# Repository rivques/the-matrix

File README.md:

# the-matrix

This is a large (theoretically 1ftx1ft) LED matrix display with a resolution of up to 120x120 monochrome pixels. My intended use for it is to act as an "ultra-clock," showing not just the time but also other useful information like weather, sports scores, maybe news, etc. However, it should be said that this is designed to be a generic module, and not destined for any specific project - this should be something I can pull off my shelf, send the correct control signals to, and get a display from.

I've had the ultra-clock idea for a while, and I originally wanted to use flip dots for the display, but they turned out to be expensive and hard to find, so I switched to using LED matrices instead.

The full display is constructed of 9 display modules, each of which itself contains 25 8x8 LED matrices. Each module also contains positions for the shift registers and MOSFETs that make up the control circuitry.

However, I have not yet built the full display - scaling up from 1 to 9 modules turned out to be _much_ harder than expected. I have 4 modules fully built, plus harnesses and a control board - I just haven't been able to make them play nice, despite spending more than 20 hours on scaling and troubleshooting. I still hope to realize the full vision at some point, but I'm pretty burnt out on this for the short term.

The display is not without its quirks. Most of these stem from either the geometric realities of trying to fit everything onto the board or a software-compensatable routing mistake that would take hours of work to fix in hardware. The biggest of these is that the current-limiting resistors aren't actually on the board but instead fly above the back of it. Also, the bottom and top row of matrices on each module are rotated 90 degrees, and every other module has pairs of rows and columns swapped (e.g. col1 connects to col2, col2->col1, col3->col4, etc.) This is something I can fix in software.

The display will probably be driven by a Pi Pico W or an ESP32, but especially if high framerates are not required it could be also driven by something less powerful. The driver connects to each row and column via the row control and column control pads.

One of the things I hope to learn from this board is where the limits actually lie when I try to drive things at high frequencies. I don't know how scared to be of things like ringing or EMI, and I'll probably find out.

The theoretical max framerate for this board is something like 4096fps, which would probably be implemented as 16fps with 255-tick BCM dimming, though this would require driving the clock line at something like 4MHz, and I have no idea if that'll be possible. If it's not, I can derate to something like 8fps with 7-tick dimming, which would be ~64fps or a much more manageable 60kHz clock frequency.

Here's a render of the back of the a single display module (the front is just a grid of matrices, which I don't have a 3D model for but I'm sure you can imagine). For more pictures, including the schematic and each internal layer, check out the [journal](https://github.com/rivques/the-matrix/blob/main/JOURNAL.md#may-29th).

BOM (for some parts I'm getting spares since they'd be a pain to source if some turn out to be dead on arrival. if this can't be included in the grant i'll happily cover the spares myself):

Part|Quantity|Price/unit|Total price|# pins/unit|# pins total|Note|Link
---|---|---|---|---|---|---|---
788AS 8x8 LED Matrix|230|$0.35|$82.00|16|3600|not going to count on 0% DoA rate here|https://www.aliexpress.us/item/2251832771187101.html
74HC595 Shift Register|15|$0.22|$4.00|16|240|2x20 is cheaper than 3x5|https://www.aliexpress.us/item/3256807421796895.html
TPIC6B595 Shift Register|20|$0.50|$10|16|240|again, not counting on no DoA|https://www.aliexpress.us/item/3256806981485001.html
IRFU9024NPBF MOSFET|125|$0.40|$40.00|3|360||https://www.aliexpress.us/item/3256808251284284.html
220Ω Resistor|120|$0.02|$2.80|2|240|2x100 is cheaper than 12x10|https://www.aliexpress.us/item/2251832766343175.html
2x20 right-angle header female|12|$2.00|$4.00|40|80||https://www.aliexpress.us/item/3256805899201197.html
2x20 right-angle header male|12|$2.50|$5.00|40|80||https://www.aliexpress.us/item/3256804718416281.html
5V 3A Power Supply|1|$4.00|$4.00|2|2||https://www.aliexpress.us/item/3256805577151044.html
Matrix PCB|10|$2.5|$25.00|0|0|i'll buy this separately from the grant so i can combine it with another order|JLCPCB
Total|||$173||4850|total w/o PCB: $148 :tada:

Schematic:

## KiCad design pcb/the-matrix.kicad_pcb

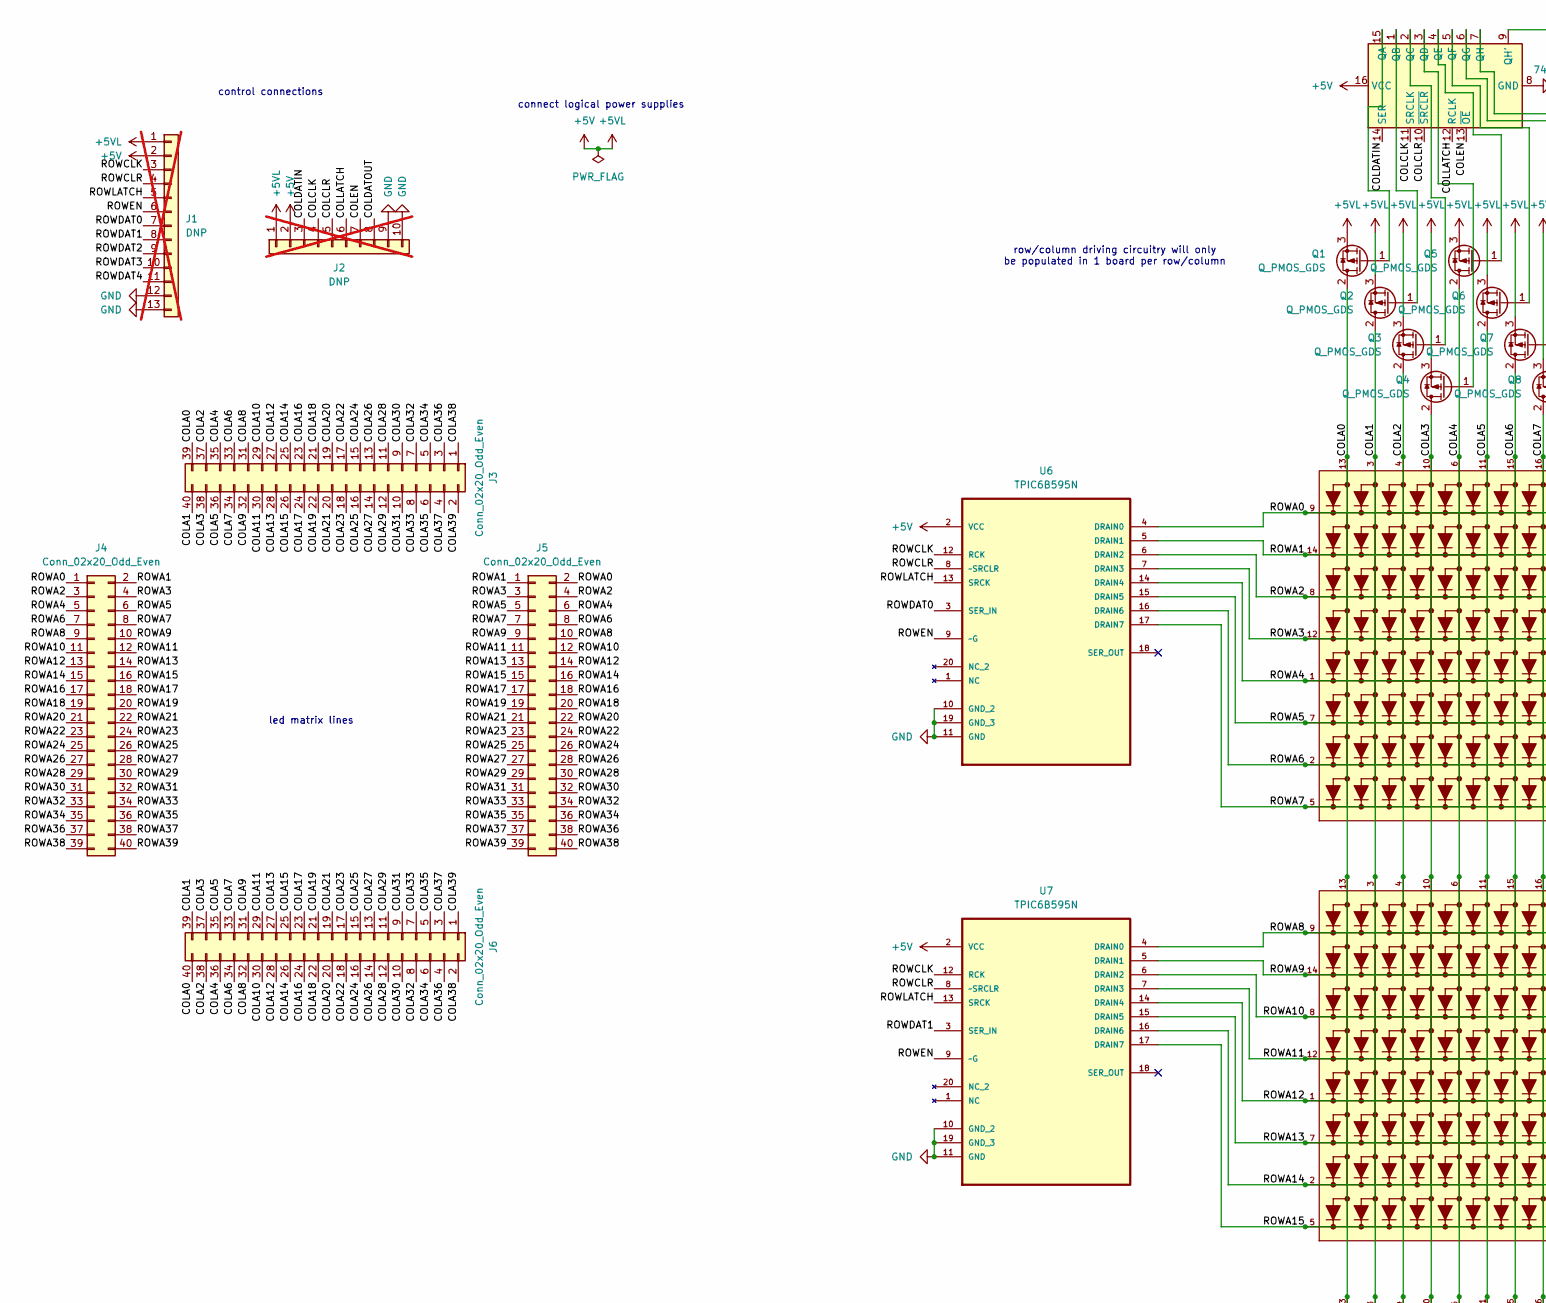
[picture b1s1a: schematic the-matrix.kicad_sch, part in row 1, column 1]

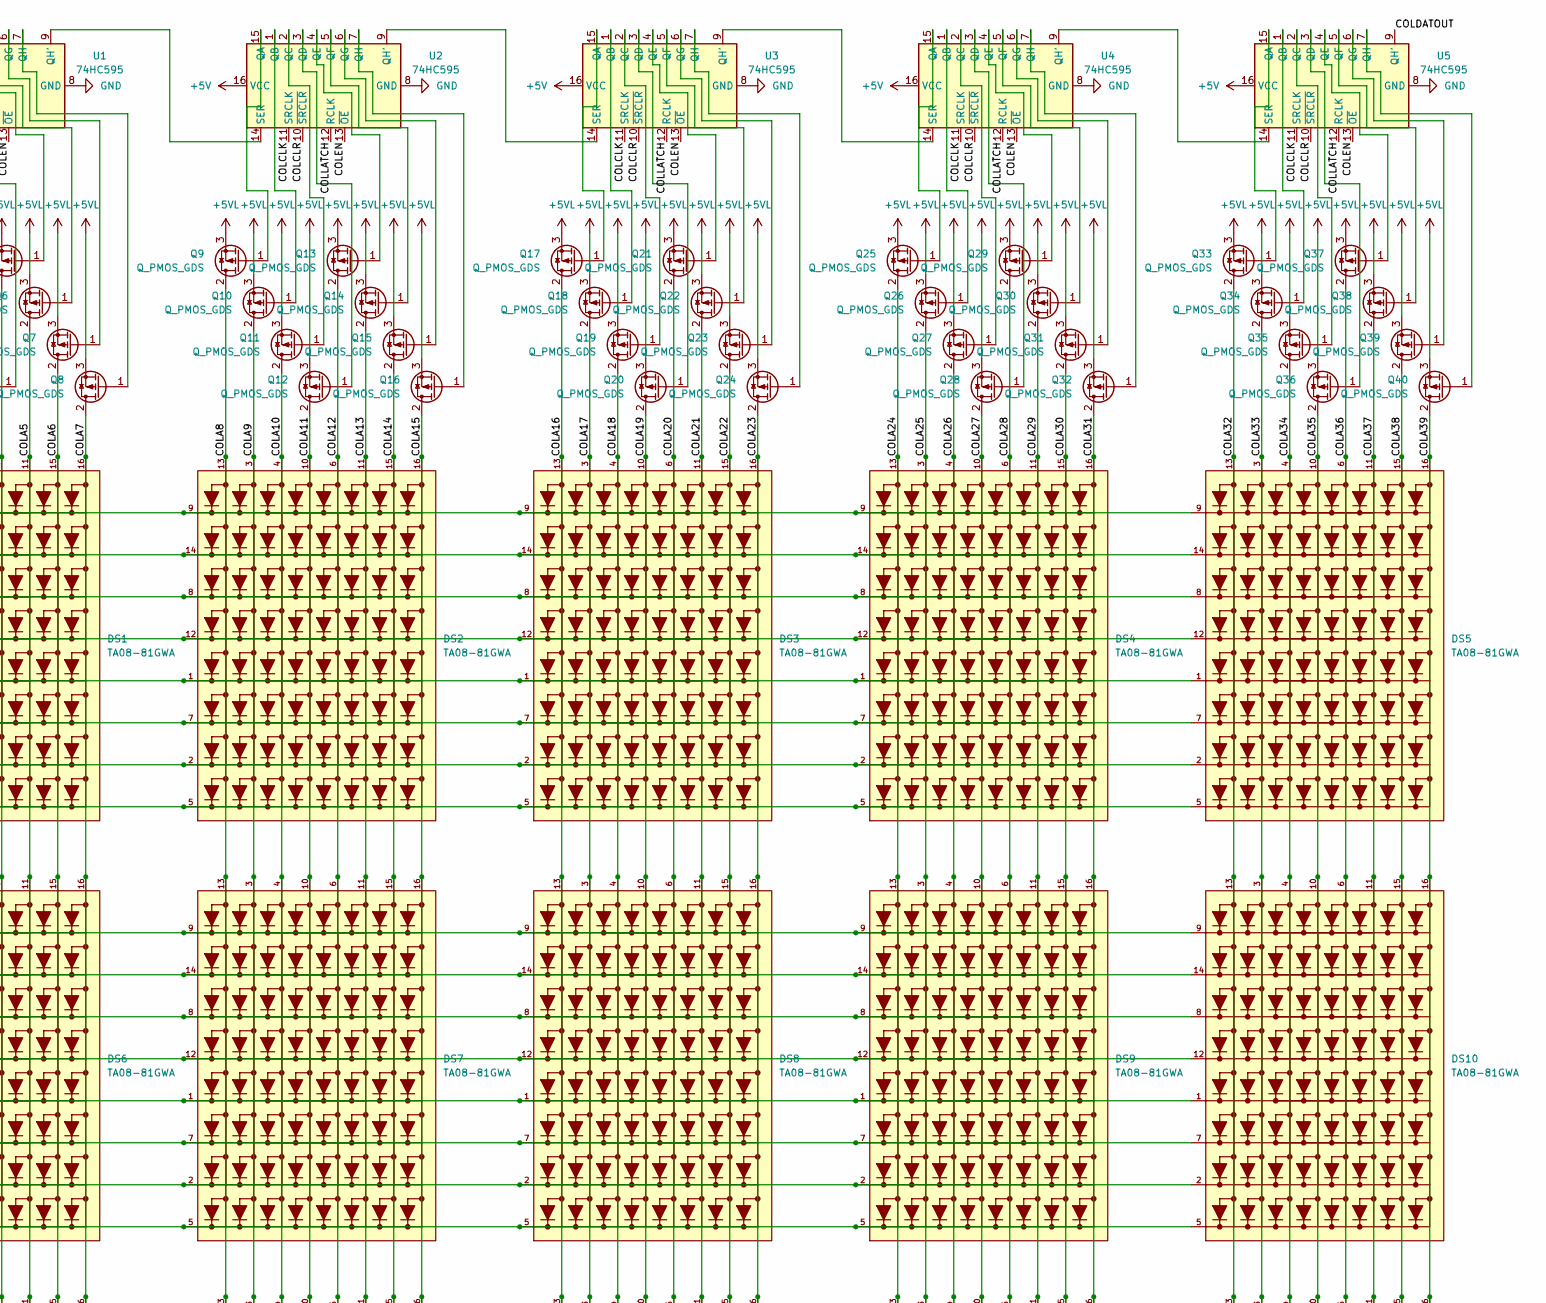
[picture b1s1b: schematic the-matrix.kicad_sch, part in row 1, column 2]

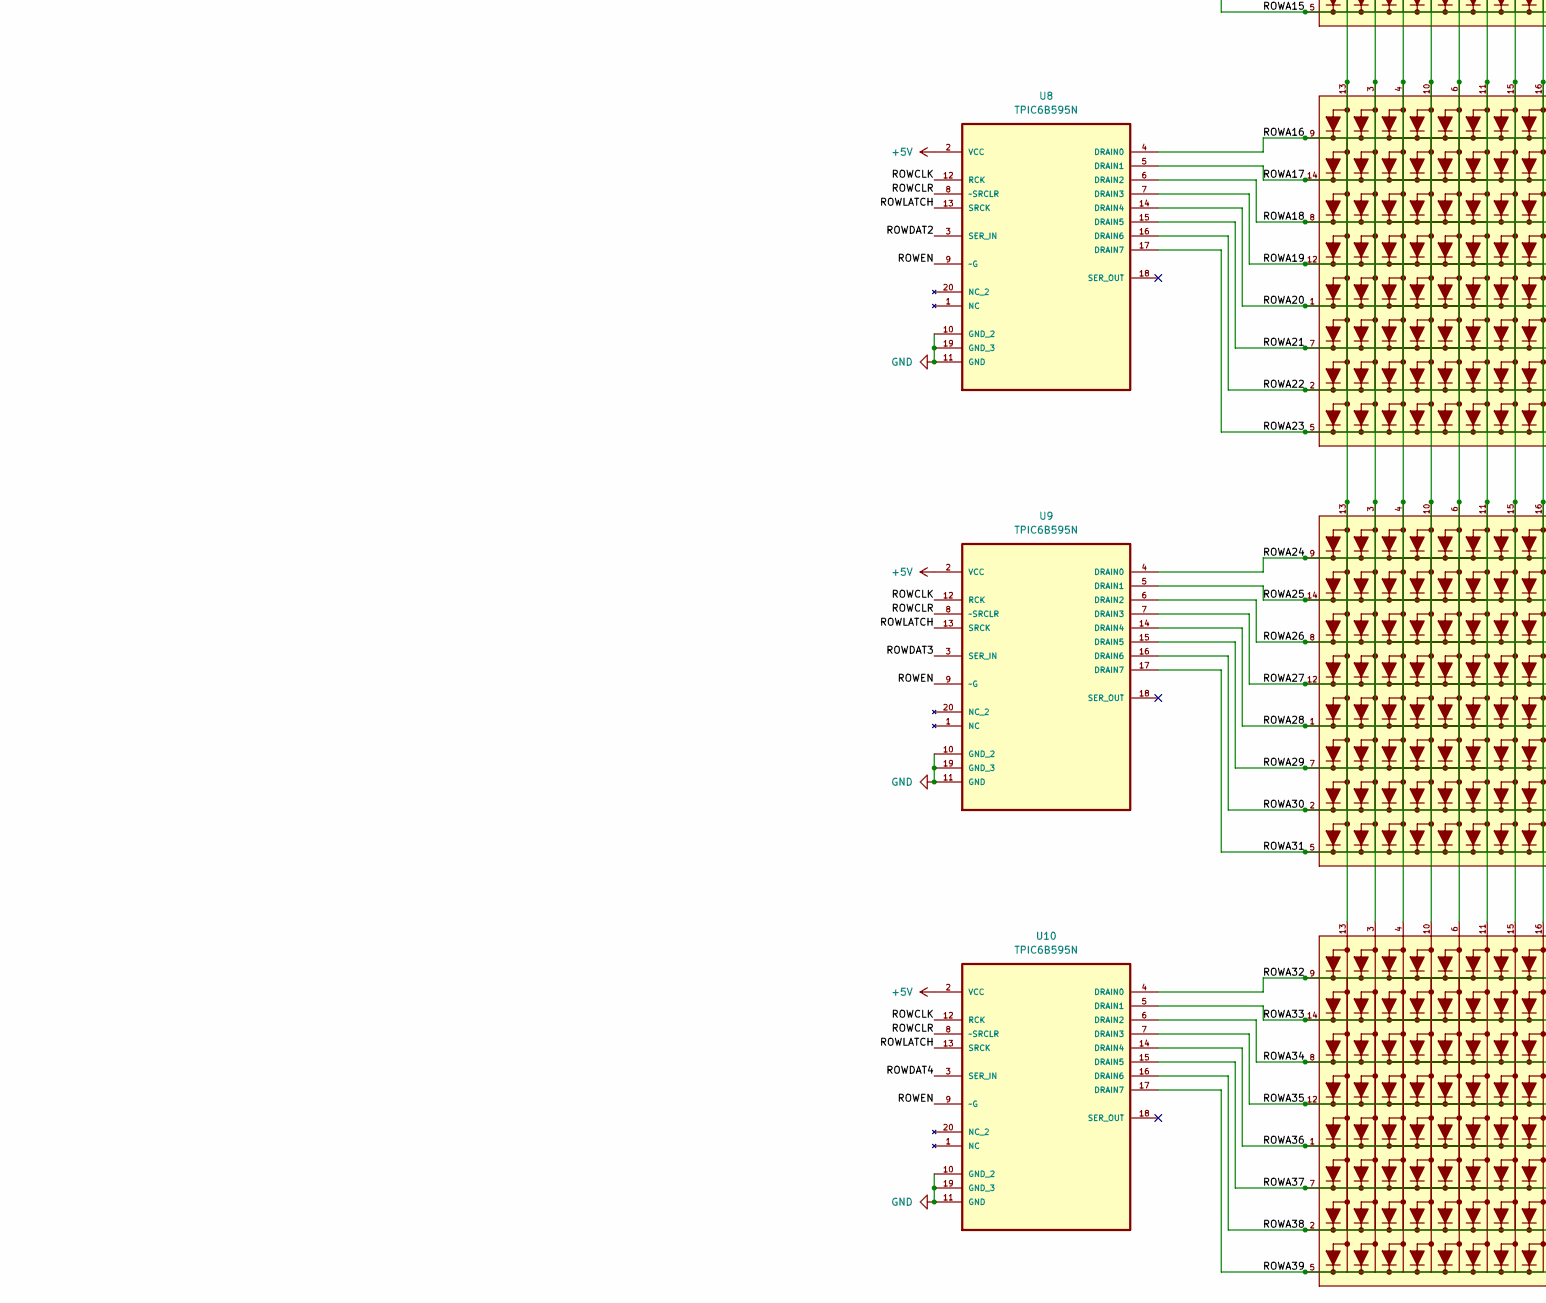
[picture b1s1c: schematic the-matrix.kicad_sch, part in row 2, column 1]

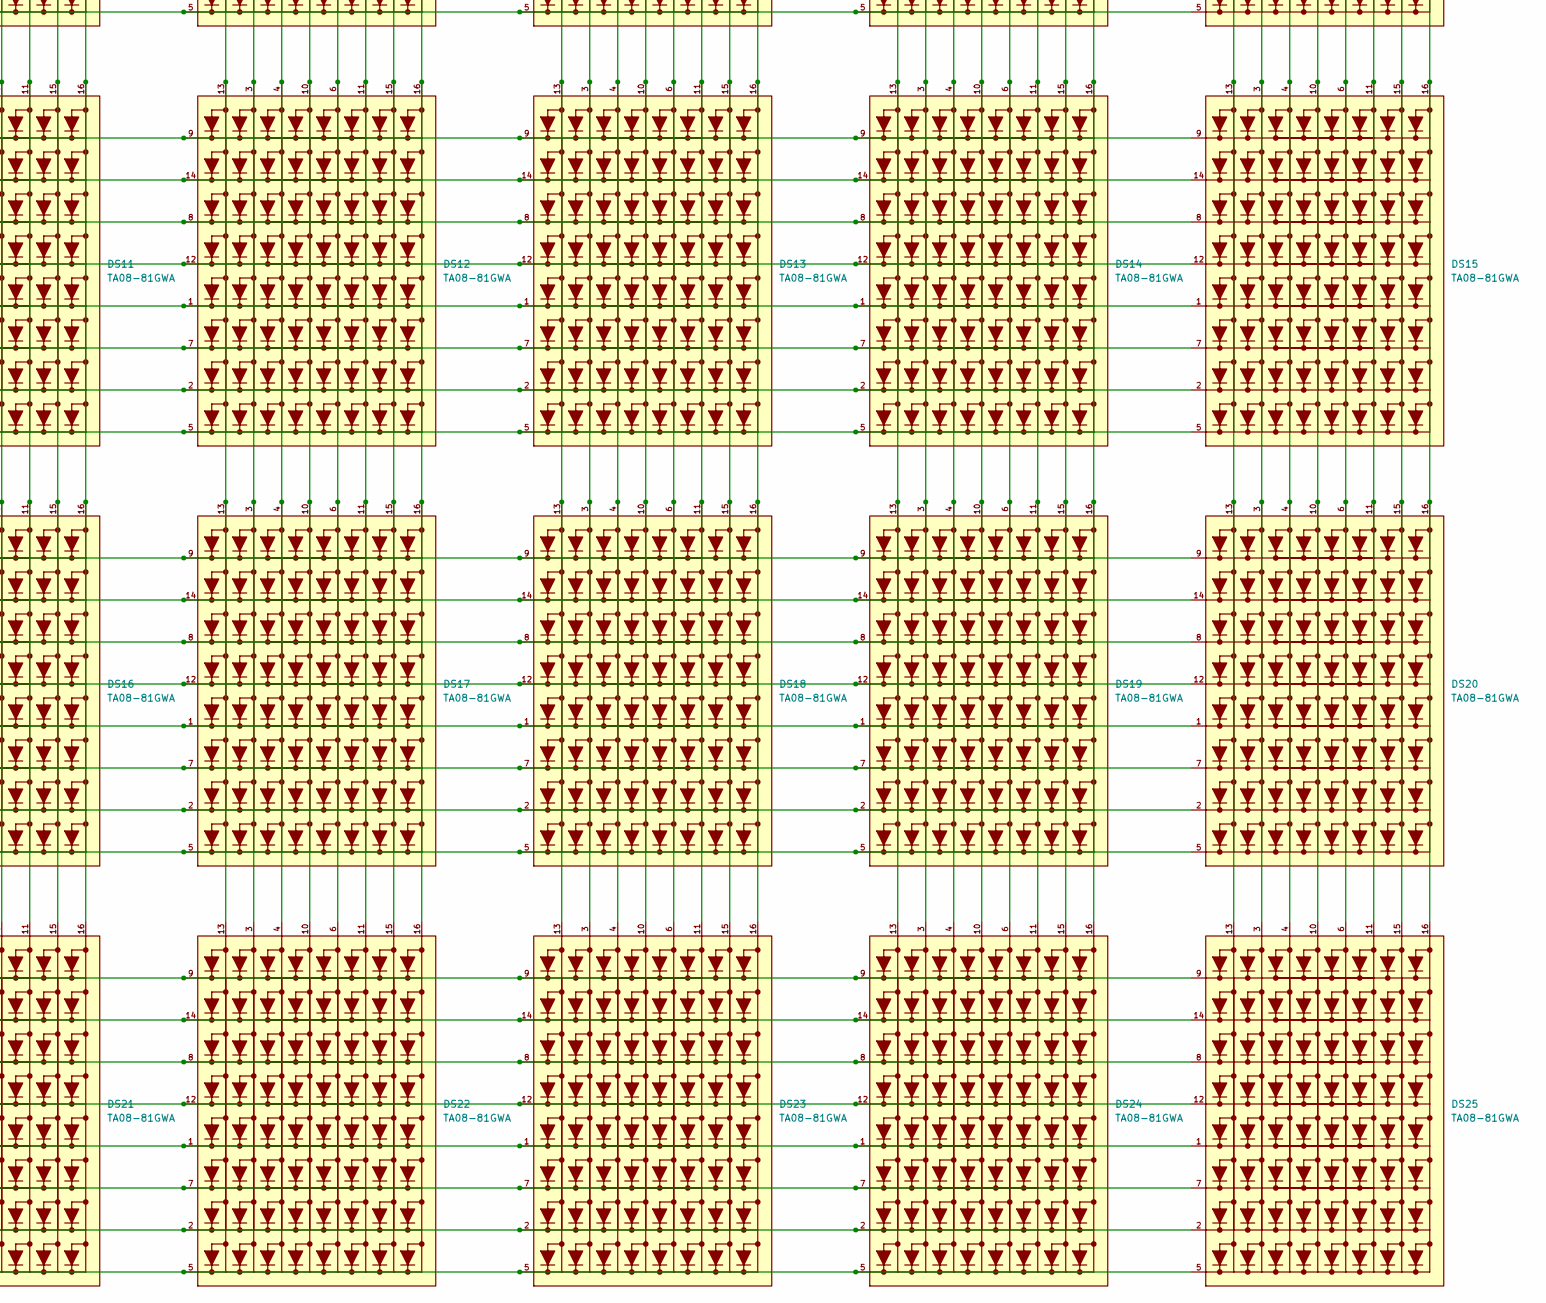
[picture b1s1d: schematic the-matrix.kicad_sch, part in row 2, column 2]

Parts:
DS1, DS2, DS3, DS4, DS5, DS6, DS7, DS8, DS9, DS10, DS11, DS12, DS13, DS14, DS15, DS16, DS17, DS18, DS19, DS20, DS21, DS22, DS23, DS24, DS25: TA08-81GWA; DISPLAY_TA08-81GWA; PARTREV V.11A
J1: DNP; PinHeader_1x13_P2.54mm_Vertical; not fitted
J2: DNP; PinHeader_1x10_P2.54mm_Vertical; not fitted
J3, J4: Conn_02x20_Odd_Even; PinHeader_2x20_P2.54mm_Horizontal
J5, J6: Conn_02x20_Odd_Even; PinSocket_2x20_P2.54mm_Horizontal
Q1, Q2, Q3, Q4, Q5, Q6, Q7, Q8, Q9, Q10, Q11, Q12, Q13, Q14, Q15, Q16, Q17, Q18, Q19, Q20, Q21, Q22, Q23, Q24, Q25, Q26, Q27, Q28, Q29, Q30, Q31, Q32, Q33, Q34, Q35, Q36, Q37, Q38, Q39, Q40: Q_PMOS_GDS; TO-251-3_Vertical_ThinPads
U1, U2, U3, U4, U5: 74HC595; DIP-16_W7.62mm
U6, U7, U8, U9, U10: TPIC6B595N; DIP-20_W7.62mm; MPN TPIC6B595N

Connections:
+5V: J1.1, J1.2, J2.1, J2.2, Q1.3 (S), Q2.3 (S), Q3.3 (S), Q4.3 (S), Q5.3 (S), Q6.3 (S), Q7.3 (S), Q8.3 (S), Q9.3 (S), Q10.3 (S), Q11.3 (S), Q12.3 (S), Q13.3 (S), Q14.3 (S), Q15.3 (S), Q16.3 (S), Q17.3 (S), Q18.3 (S), Q19.3 (S), Q20.3 (S), Q21.3 (S), Q22.3 (S), Q23.3 (S), Q24.3 (S), Q25.3 (S), Q26.3 (S), Q27.3 (S), Q28.3 (S), Q29.3 (S), Q30.3 (S), Q31.3 (S), Q32.3 (S), Q33.3 (S), Q34.3 (S), Q35.3 (S), Q36.3 (S), Q37.3 (S), Q38.3 (S), Q39.3 (S), Q40.3 (S), U1.16 (VCC), U2.16 (VCC), U3.16 (VCC), U4.16 (VCC), U5.16 (VCC), U6.2 (VCC), U7.2 (VCC), U8.2 (VCC), U9.2 (VCC), U10.2 (VCC)
/COLA0: DS1.13, DS6.13, DS11.13, DS16.13, DS21.13, J3.39, J6.40, Q1.2 (D)
/COLA1: DS1.3, DS6.3, DS11.3, DS16.3, DS21.3, J3.40, J6.39, Q2.2 (D)
/COLA2: DS1.4, DS6.4, DS11.4, DS16.4, DS21.4, J3.37, J6.38, Q3.2 (D)
/COLA3: DS1.10, DS6.10, DS11.10, DS16.10, DS21.10, J3.38, J6.37, Q4.2 (D)
/COLA4: DS1.6, DS6.6, DS11.6, DS16.6, DS21.6, J3.35, J6.36, Q5.2 (D)
/COLA5: DS1.11, DS6.11, DS11.11, DS16.11, DS21.11, J3.36, J6.35, Q6.2 (D)
/COLA6: DS1.15, DS6.15, DS11.15, DS16.15, DS21.15, J3.33, J6.34, Q7.2 (D)
/COLA7: DS1.16, DS6.16, DS11.16, DS16.16, DS21.16, J3.34, J6.33, Q8.2 (D)
/COLA8: DS2.13, DS7.13, DS12.13, DS17.13, DS22.13, J3.31, J6.32, Q9.2 (D)
/COLA9: DS2.3, DS7.3, DS12.3, DS17.3, DS22.3, J3.32, J6.31, Q10.2 (D)
/COLA10: DS2.4, DS7.4, DS12.4, DS17.4, DS22.4, J3.29, J6.30, Q11.2 (D)
/COLA11: DS2.10, DS7.10, DS12.10, DS17.10, DS22.10, J3.30, J6.29, Q12.2 (D)
/COLA12: DS2.6, DS7.6, DS12.6, DS17.6, DS22.6, J3.27, J6.28, Q13.2 (D)
/COLA13: DS2.11, DS7.11, DS12.11, DS17.11, DS22.11, J3.28, J6.27, Q14.2 (D)
/COLA14: DS2.15, DS7.15, DS12.15, DS17.15, DS22.15, J3.25, J6.26, Q15.2 (D)
/COLA15: DS2.16, DS7.16, DS12.16, DS17.16, DS22.16, J3.26, J6.25, Q16.2 (D)
/COLA16: DS3.13, DS8.13, DS13.13, DS18.13, DS23.13, J3.23, J6.24, Q17.2 (D)
/COLA17: DS3.3, DS8.3, DS13.3, DS18.3, DS23.3, J3.24, J6.23, Q18.2 (D)
/COLA18: DS3.4, DS8.4, DS13.4, DS18.4, DS23.4, J3.21, J6.22, Q19.2 (D)
/COLA19: DS3.10, DS8.10, DS13.10, DS18.10, DS23.10, J3.22, J6.21, Q20.2 (D)
/COLA20: DS3.6, DS8.6, DS13.6, DS18.6, DS23.6, J3.19, J6.20, Q21.2 (D)
/COLA21: DS3.11, DS8.11, DS13.11, DS18.11, DS23.11, J3.20, J6.19, Q22.2 (D)
/COLA22: DS3.15, DS8.15, DS13.15, DS18.15, DS23.15, J3.17, J6.18, Q23.2 (D)
/COLA23: DS3.16, DS8.16, DS13.16, DS18.16, DS23.16, J3.18, J6.17, Q24.2 (D)
/COLA24: DS4.13, DS9.13, DS14.13, DS19.13, DS24.13, J3.15, J6.16, Q25.2 (D)
/COLA25: DS4.3, DS9.3, DS14.3, DS19.3, DS24.3, J3.16, J6.15, Q26.2 (D)
/COLA26: DS4.4, DS9.4, DS14.4, DS19.4, DS24.4, J3.13, J6.14, Q27.2 (D)
/COLA27: DS4.10, DS9.10, DS14.10, DS19.10, DS24.10, J3.14, J6.13, Q28.2 (D)
/COLA28: DS4.6, DS9.6, DS14.6, DS19.6, DS24.6, J3.11, J6.12, Q29.2 (D)
/COLA29: DS4.11, DS9.11, DS14.11, DS19.11, DS24.11, J3.12, J6.11, Q30.2 (D)
/COLA30: DS4.15, DS9.15, DS14.15, DS19.15, DS24.15, J3.9, J6.10, Q31.2 (D)
/COLA31: DS4.16, DS9.16, DS14.16, DS19.16, DS24.16, J3.10, J6.9, Q32.2 (D)
/COLA32: DS5.13, DS10.13, DS15.13, DS20.13, DS25.13, J3.7, J6.8, Q33.2 (D)
/COLA33: DS5.3, DS10.3, DS15.3, DS20.3, DS25.3, J3.8, J6.7, Q34.2 (D)
/COLA34: DS5.4, DS10.4, DS15.4, DS20.4, DS25.4, J3.5, J6.6, Q35.2 (D)
/COLA35: DS5.10, DS10.10, DS15.10, DS20.10, DS25.10, J3.6, J6.5, Q36.2 (D)
/COLA36: DS5.6, DS10.6, DS15.6, DS20.6, DS25.6, J3.3, J6.4, Q37.2 (D)
/COLA37: DS5.11, DS10.11, DS15.11, DS20.11, DS25.11, J3.4, J6.3, Q38.2 (D)
/COLA38: DS5.15, DS10.15, DS15.15, DS20.15, DS25.15, J3.1, J6.2, Q39.2 (D)
/COLA39: DS5.16, DS10.16, DS15.16, DS20.16, DS25.16, J3.2, J6.1, Q40.2 (D)
/COLCLK: J2.4, U1.11 (SRCLK), U2.11 (SRCLK), U3.11 (SRCLK), U4.11 (SRCLK), U5.11 (SRCLK)
/COLCLR: J2.5, U1.10 (~SRCLR), U2.10 (~SRCLR), U3.10 (~SRCLR), U4.10 (~SRCLR), U5.10 (~SRCLR)
/COLDATIN: J2.3, U1.14 (SER)
/COLDATOUT: J2.8, U5.9 (QH')
/COLEN: J2.7, U1.13 (~OE), U2.13 (~OE), U3.13 (~OE), U4.13 (~OE), U5.13 (~OE)
/COLLATCH: J2.6, U1.12 (RCLK), U2.12 (RCLK), U3.12 (RCLK), U4.12 (RCLK), U5.12 (RCLK)
/ROWA0: DS1.9, DS2.9, DS3.9, DS4.9, DS5.9, J4.1, J5.2, U6.4 (DRAIN0)
/ROWA1: DS1.14, DS2.14, DS3.14, DS4.14, DS5.14, J4.2, J5.1, U6.5 (DRAIN1)
/ROWA2: DS1.8, DS2.8, DS3.8, DS4.8, DS5.8, J4.3, J5.4, U6.6 (DRAIN2)
/ROWA3: DS1.12, DS2.12, DS3.12, DS4.12, DS5.12, J4.4, J5.3, U6.7 (DRAIN3)
/ROWA4: DS1.1, DS2.1, DS3.1, DS4.1, DS5.1, J4.5, J5.6, U6.14 (DRAIN4)
/ROWA5: DS1.7, DS2.7, DS3.7, DS4.7, DS5.7, J4.6, J5.5, U6.15 (DRAIN5)
/ROWA6: DS1.2, DS2.2, DS3.2, DS4.2, DS5.2, J4.7, J5.8, U6.16 (DRAIN6)
/ROWA7: DS1.5, DS2.5, DS3.5, DS4.5, DS5.5, J4.8, J5.7, U6.17 (DRAIN7)
/ROWA8: DS6.9, DS7.9, DS8.9, DS9.9, DS10.9, J4.9, J5.10, U7.4 (DRAIN0)
/ROWA9: DS6.14, DS7.14, DS8.14, DS9.14, DS10.14, J4.10, J5.9, U7.5 (DRAIN1)
/ROWA10: DS6.8, DS7.8, DS8.8, DS9.8, DS10.8, J4.11, J5.12, U7.6 (DRAIN2)
/ROWA11: DS6.12, DS7.12, DS8.12, DS9.12, DS10.12, J4.12, J5.11, U7.7 (DRAIN3)
/ROWA12: DS6.1, DS7.1, DS8.1, DS9.1, DS10.1, J4.13, J5.14, U7.14 (DRAIN4)
/ROWA13: DS6.7, DS7.7, DS8.7, DS9.7, DS10.7, J4.14, J5.13, U7.15 (DRAIN5)
/ROWA14: DS6.2, DS7.2, DS8.2, DS9.2, DS10.2, J4.15, J5.16, U7.16 (DRAIN6)
/ROWA15: DS6.5, DS7.5, DS8.5, DS9.5, DS10.5, J4.16, J5.15, U7.17 (DRAIN7)
/ROWA16: DS11.9, DS12.9, DS13.9, DS14.9, DS15.9, J4.17, J5.18, U8.4 (DRAIN0)
/ROWA17: DS11.14, DS12.14, DS13.14, DS14.14, DS15.14, J4.18, J5.17, U8.5 (DRAIN1)
/ROWA18: DS11.8, DS12.8, DS13.8, DS14.8, DS15.8, J4.19, J5.20, U8.6 (DRAIN2)
/ROWA19: DS11.12, DS12.12, DS13.12, DS14.12, DS15.12, J4.20, J5.19, U8.7 (DRAIN3)
/ROWA20: DS11.1, DS12.1, DS13.1, DS14.1, DS15.1, J4.21, J5.22, U8.14 (DRAIN4)
/ROWA21: DS11.7, DS12.7, DS13.7, DS14.7, DS15.7, J4.22, J5.21, U8.15 (DRAIN5)
/ROWA22: DS11.2, DS12.2, DS13.2, DS14.2, DS15.2, J4.23, J5.24, U8.16 (DRAIN6)
/ROWA23: DS11.5, DS12.5, DS13.5, DS14.5, DS15.5, J4.24, J5.23, U8.17 (DRAIN7)
/ROWA24: DS16.9, DS17.9, DS18.9, DS19.9, DS20.9, J4.25, J5.26, U9.4 (DRAIN0)
/ROWA25: DS16.14, DS17.14, DS18.14, DS19.14, DS20.14, J4.26, J5.25, U9.5 (DRAIN1)
/ROWA26: DS16.8, DS17.8, DS18.8, DS19.8, DS20.8, J4.27, J5.28, U9.6 (DRAIN2)
/ROWA27: DS16.12, DS17.12, DS18.12, DS19.12, DS20.12, J4.28, J5.27, U9.7 (DRAIN3)
/ROWA28: DS16.1, DS17.1, DS18.1, DS19.1, DS20.1, J4.29, J5.30, U9.14 (DRAIN4)
/ROWA29: DS16.7, DS17.7, DS18.7, DS19.7, DS20.7, J4.30, J5.29, U9.15 (DRAIN5)
/ROWA30: DS16.2, DS17.2, DS18.2, DS19.2, DS20.2, J4.31, J5.32, U9.16 (DRAIN6)
/ROWA31: DS16.5, DS17.5, DS18.5, DS19.5, DS20.5, J4.32, J5.31, U9.17 (DRAIN7)
/ROWA32: DS21.9, DS22.9, DS23.9, DS24.9, DS25.9, J4.33, J5.34, U10.4 (DRAIN0)
/ROWA33: DS21.14, DS22.14, DS23.14, DS24.14, DS25.14, J4.34, J5.33, U10.5 (DRAIN1)
/ROWA34: DS21.8, DS22.8, DS23.8, DS24.8, DS25.8, J4.35, J5.36, U10.6 (DRAIN2)
/ROWA35: DS21.12, DS22.12, DS23.12, DS24.12, DS25.12, J4.36, J5.35, U10.7 (DRAIN3)
/ROWA36: DS21.1, DS22.1, DS23.1, DS24.1, DS25.1, J4.37, J5.38, U10.14 (DRAIN4)
/ROWA37: DS21.7, DS22.7, DS23.7, DS24.7, DS25.7, J4.38, J5.37, U10.15 (DRAIN5)
/ROWA38: DS21.2, DS22.2, DS23.2, DS24.2, DS25.2, J4.39, J5.40, U10.16 (DRAIN6)
/ROWA39: DS21.5, DS22.5, DS23.5, DS24.5, DS25.5, J4.40, J5.39, U10.17 (DRAIN7)
/ROWCLK: J1.3, U6.12 (RCK), U7.12 (RCK), U8.12 (RCK), U9.12 (RCK), U10.12 (RCK)
/ROWCLR: J1.4, U6.8 (~SRCLR), U7.8 (~SRCLR), U8.8 (~SRCLR), U9.8 (~SRCLR), U10.8 (~SRCLR)
/ROWDAT0: J1.7, U6.3 (SER_IN)
/ROWDAT1: J1.8, U7.3 (SER_IN)
/ROWDAT2: J1.9, U8.3 (SER_IN)
/ROWDAT3: J1.10, U9.3 (SER_IN)
/ROWDAT4: J1.11, U10.3 (SER_IN)
/ROWEN: J1.6, U6.9 (~G), U7.9 (~G), U8.9 (~G), U9.9 (~G), U10.9 (~G)
/ROWLATCH: J1.5, U6.13 (SRCK), U7.13 (SRCK), U8.13 (SRCK), U9.13 (SRCK), U10.13 (SRCK)
GND: J1.12, J1.13, J2.9, J2.10, U1.8 (GND), U2.8 (GND), U3.8 (GND), U4.8 (GND), U5.8 (GND), U6.10 (GND_2), U6.11 (GND), U6.19 (GND_3), U7.10 (GND_2), U7.11 (GND), U7.19 (GND_3), U8.10 (GND_2), U8.11 (GND), U8.19 (GND_3), U9.10 (GND_2), U9.11 (GND), U9.19 (GND_3), U10.10 (GND_2), U10.11 (GND), U10.19 (GND_3)
unnamed: Q1.1 (G), U1.15 (QA)
unnamed: Q2.1 (G), U1.1 (QB)
unnamed: Q3.1 (G), U1.2 (QC)
unnamed: Q4.1 (G), U1.3 (QD)
unnamed: Q5.1 (G), U1.4 (QE)
unnamed: Q6.1 (G), U1.5 (QF)
unnamed: Q7.1 (G), U1.6 (QG)
unnamed: Q8.1 (G), U1.7 (QH)
unnamed: Q9.1 (G), U2.15 (QA)
unnamed: Q10.1 (G), U2.1 (QB)
unnamed: Q11.1 (G), U2.2 (QC)
unnamed: Q12.1 (G), U2.3 (QD)
unnamed: Q13.1 (G), U2.4 (QE)
unnamed: Q14.1 (G), U2.5 (QF)
unnamed: Q15.1 (G), U2.6 (QG)
unnamed: Q16.1 (G), U2.7 (QH)
unnamed: Q17.1 (G), U3.15 (QA)
unnamed: Q18.1 (G), U3.1 (QB)
unnamed: Q19.1 (G), U3.2 (QC)
unnamed: Q20.1 (G), U3.3 (QD)
unnamed: Q21.1 (G), U3.4 (QE)
unnamed: Q22.1 (G), U3.5 (QF)
unnamed: Q23.1 (G), U3.6 (QG)
unnamed: Q24.1 (G), U3.7 (QH)
unnamed: Q25.1 (G), U4.15 (QA)
unnamed: Q26.1 (G), U4.1 (QB)
unnamed: Q27.1 (G), U4.2 (QC)
unnamed: Q28.1 (G), U4.3 (QD)
unnamed: Q29.1 (G), U4.4 (QE)
unnamed: Q30.1 (G), U4.5 (QF)
unnamed: Q31.1 (G), U4.6 (QG)
unnamed: Q32.1 (G), U4.7 (QH)
unnamed: Q33.1 (G), U5.15 (QA)
unnamed: Q34.1 (G), U5.1 (QB)
unnamed: Q35.1 (G), U5.2 (QC)
unnamed: Q36.1 (G), U5.3 (QD)
unnamed: Q37.1 (G), U5.4 (QE)
unnamed: Q38.1 (G), U5.5 (QF)
unnamed: Q39.1 (G), U5.6 (QG)
unnamed: Q40.1 (G), U5.7 (QH)
unnamed: U1.9 (QH'), U2.14 (SER)
unnamed: U2.9 (QH'), U3.14 (SER)
unnamed: U3.9 (QH'), U4.14 (SER)
unnamed: U4.9 (QH'), U5.14 (SER)

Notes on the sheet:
connect logical power supplies
row/column driving circuitry will only be populated in 1 board per row/column
control connections
led matrix lines

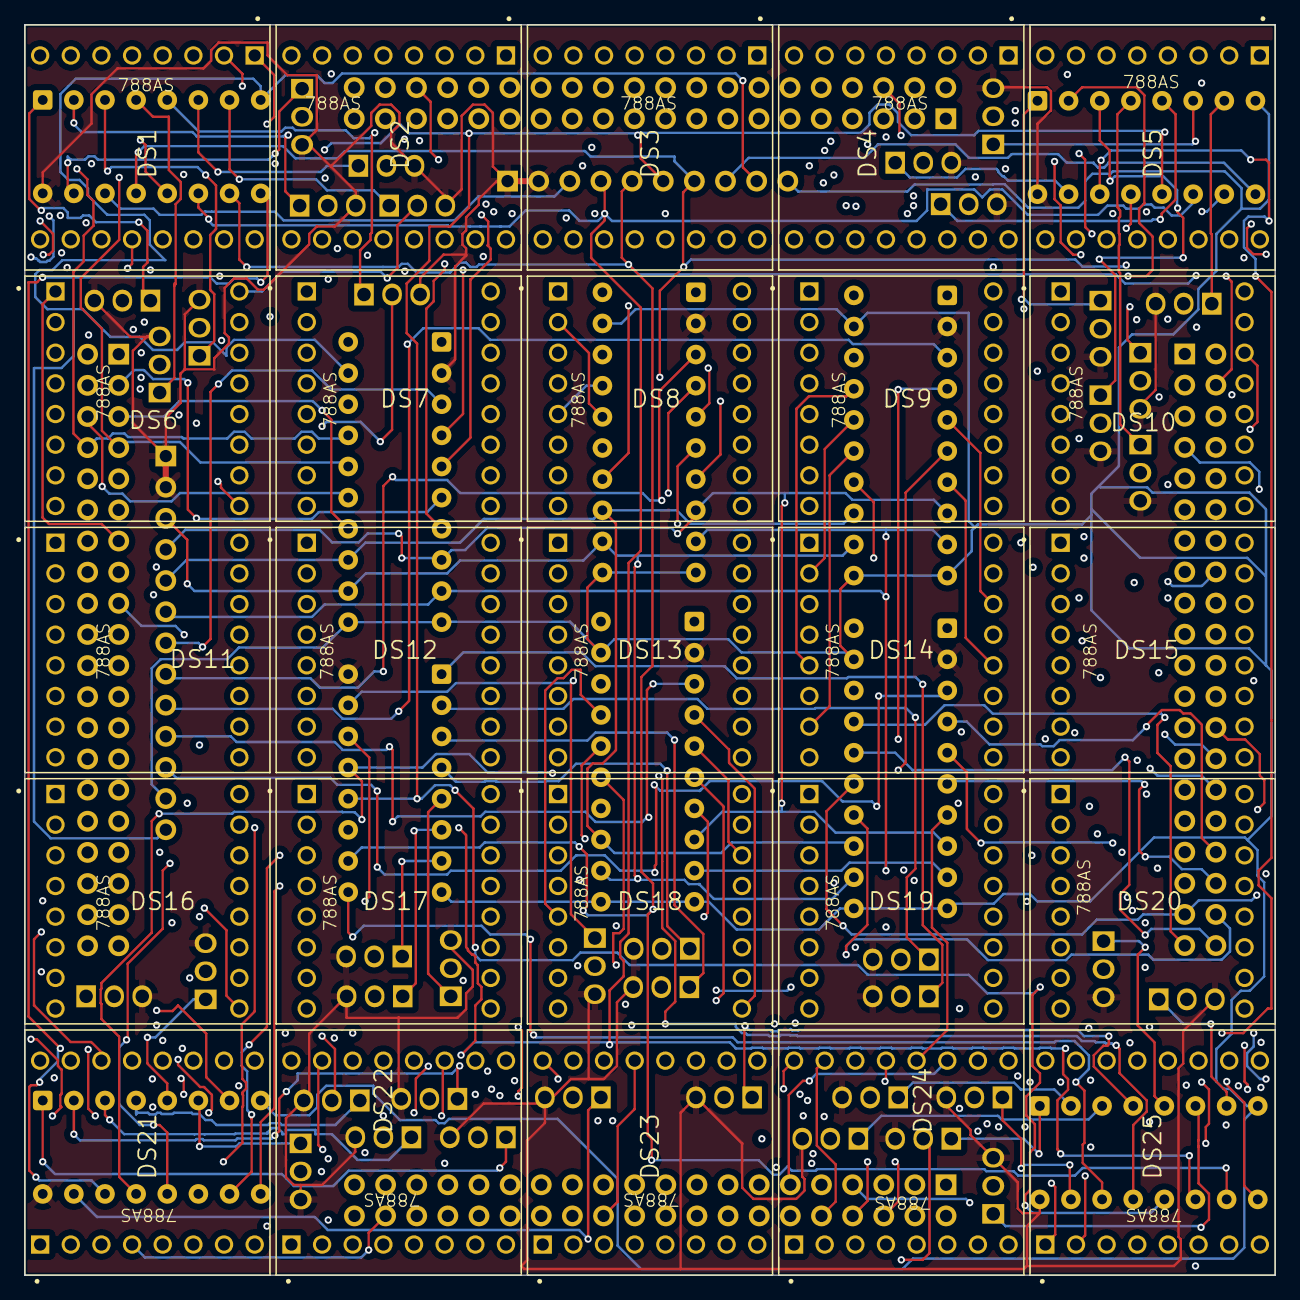
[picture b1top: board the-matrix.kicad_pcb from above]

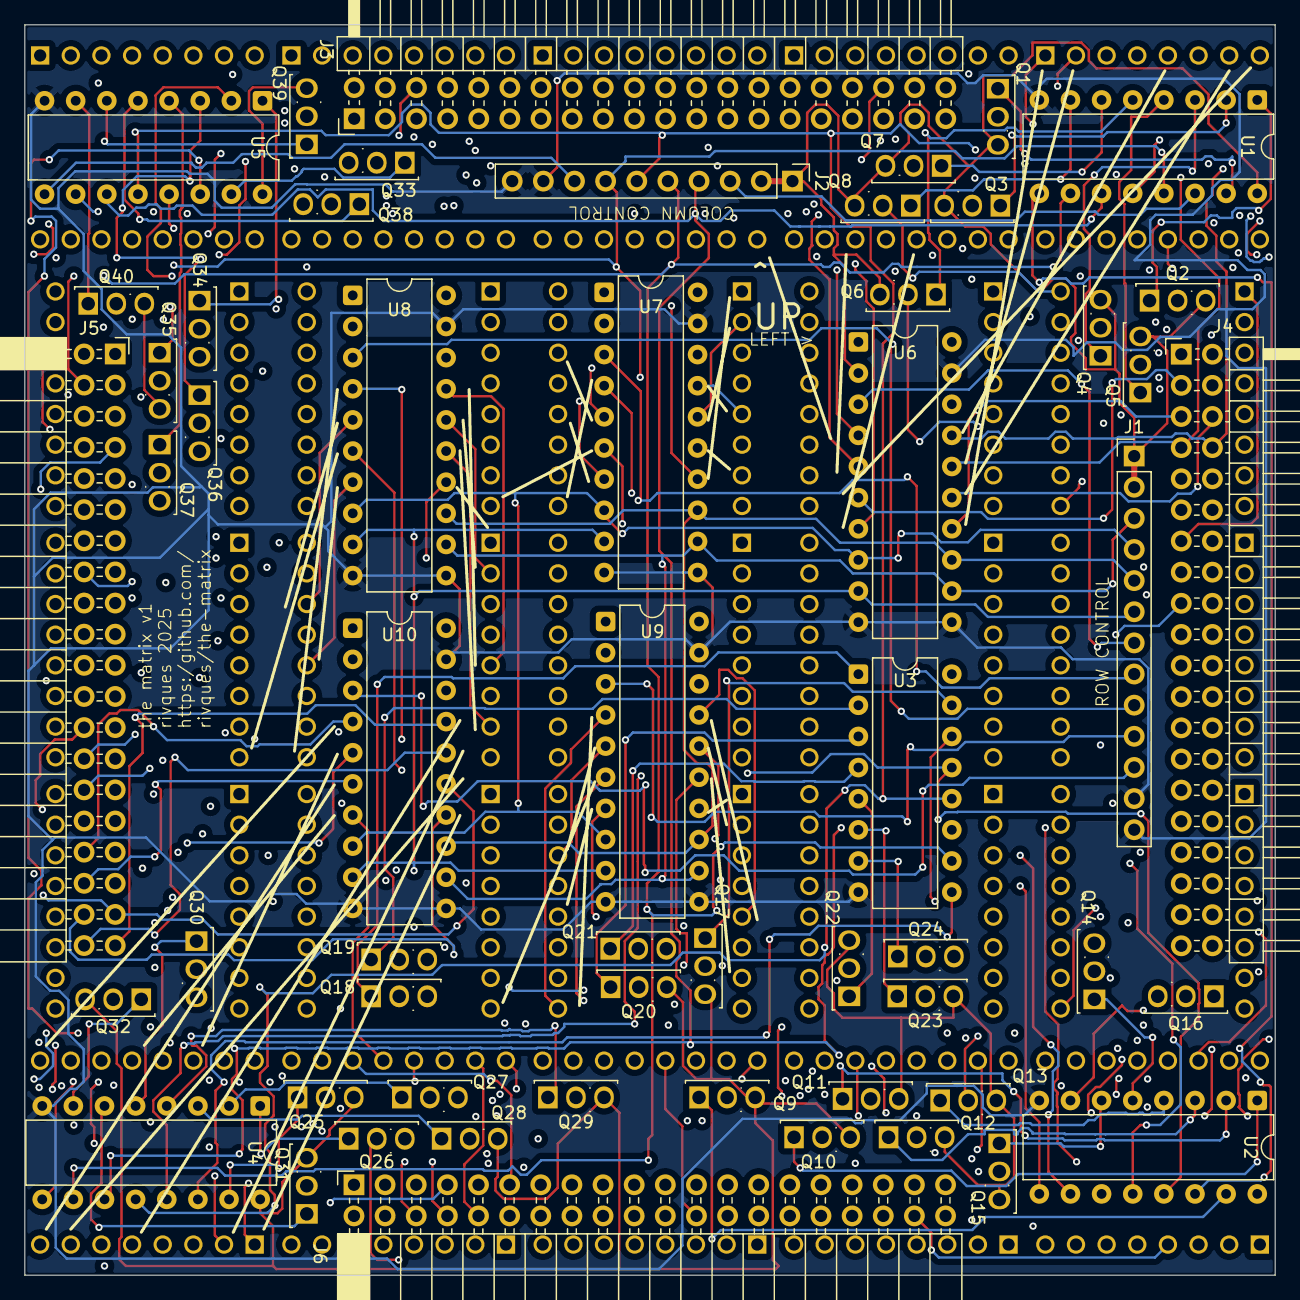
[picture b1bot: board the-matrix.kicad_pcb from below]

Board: 4 copper layers, 102.0 x 102.0 mm, 81 parts (56 on the bottom side), 141 nets.

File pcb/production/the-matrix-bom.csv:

"Id";"Designator";"Footprint";"Quantity";"Designation";"Supplier and ref";
1;"DS5,DS3,DS18,DS2,DS6,DS12,DS1,DS19,DS22,DS25,DS8,DS17,DS16,DS13,DS9,DS11,DS4,DS15,DS24,DS23,DS20,DS7,DS14,DS21,DS10";"DISPLAY_TA08-81GWA";25;"TA08-81GWA";;;
2;"Q13,Q6,Q26,Q39,Q36,Q11,Q22,Q38,Q33,Q14,Q5,Q15,Q10,Q28,Q17,Q21,Q34,Q31,Q9,Q24,Q3,Q16,Q4,Q29,Q25,Q30,Q37,Q1,Q7,Q18,Q8,Q32,Q40,Q27,Q20,Q19,Q12,Q23,Q2,Q35";"TO-251-3_Vertical_ThinPads";40;"Q_PMOS_GDS";;;
3;"U6,U8,U9,U10,U7";"DIP-20_W7.62mm";5;"TPIC6B595N";;;
4;"J6,J5";"PinSocket_2x20_P2.54mm_Horizontal";2;"Conn_02x20_Odd_Even";;;
5;"U3,U4,U1,U2,U5";"DIP-16_W7.62mm";5;"74HC595";;;
6;"J4,J3";"PinHeader_2x20_P2.54mm_Horizontal";2;"Conn_02x20_Odd_Even";;;
7;"J2";"PinHeader_1x10_P2.54mm_Vertical";1;"DNP";;;
8;"J1";"PinHeader_1x13_P2.54mm_Vertical";1;"DNP";;;

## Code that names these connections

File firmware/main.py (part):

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    def __init__(self):
        self.rowdat_pins = [Pin(1, Pin.OUT)]
        self.coldat_pin = Pin(16, Pin.OUT)
        self.latch_pin = Pin(17, Pin.OUT) # NOTE: The pin labels for ROWLATCH and ROWCLK are the wrong way around. Because of this, this pin should connect to the wires labeled ROWCLK and COLLATCH.
        self.latch_pin.value(0)
        self.clear_pin = Pin(18, Pin.OUT) # active low
        self.clear_pin.value(1)
        self.rowclk_pin = Pin(19, Pin.OUT) # NOTE: Because of the above swap, this pin should connect to the wire labeled ROWLATCH.
        self.rowclk_pin.value(0)
        self.colclk_pin = Pin(20, Pin.OUT)
        self.colclk_pin.value(0)
        self.rowen_pin = PWM(Pin(0, Pin.OUT), freq=10_000_000, duty_u16=0)
        self.rowen_pin.duty_u16(65535) # disable output for now
        self.brightness = 0.5

        # clear registers
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        # shift ones through the columns
        self.coldat_pin.value(1)
        for _ in range(NUM_COLS):
            self.colclk_pin.value(1)
            utime.sleep_us(10)
            self.colclk_pin.value(0)
            utime.sleep_us(10)
        self.latch_pin.value(1)
        utime.sleep_us(10)
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            #  latch the data

            # enable output
            self.rowen_pin.duty_u16(int((1-self.brightness) * 65535))
            self.brightness += 0.01
            if self.brightness > 0.7:
                self.brightness = 0.0
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                            pin.value(0)
                    utime.sleep_us(5*SLOWDOWN_CONST)
                    # shift out the row data
                    self.rowclk_pin.value(1)
                    utime.sleep_us(10*SLOWDOWN_CONST)
                    self.rowclk_pin.value(0)
                    utime.sleep_us(10*SLOWDOWN_CONST)
                # shift out the column data
                if col == 0:
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                    self.coldat_pin.value(1)
                    # print("  Setting coldat pin HIGH")
                utime.sleep_us(5*SLOWDOWN_CONST)
                self.colclk_pin.value(1)
                utime.sleep_us(10*SLOWDOWN_CONST)
                self.colclk_pin.value(0)
                utime.sleep_us(10*SLOWDOWN_CONST)
                # latch the data
                self.latch_pin.value(1)
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            # print("Frame displayed.")
        finally:
            # disable output
            self.rowen_pin.duty_u16(65535)
            # print("Output disabled.")
    
    def display_pio(self, frame, pio_freq):
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        row_data.append("#" if byte else ".")
    print("".join(row_data))

matrix.rowen_pin.duty_u16(32000)

pio_freq = 400_000  # PIO frequency
pio_data_pre = array('H', [])
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    matrix.dma.active(0)
    matrix.pio.active(0)
    matrix.dma.close()
    matrix.rowen_pin.duty_u16(65535)  # disable output
    print("DMA and PIO deactivated.")
    raise
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
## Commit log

2025-05-27 initial journal
2025-05-28 schematic!
2025-05-28 add time estimates to journal (oops)
2025-05-28 add screenshots to journal
2025-05-28 quick commit so i can add a photo on gh
2025-05-28 add said image
2025-05-28 one more session for today
2025-05-28 add picture to journal
2025-05-28 it is not in fact cheaper from digikey
2025-05-28 an amount of progress on routing
2025-05-28 route the matrix
2025-05-28 more routing!
2025-05-28 column connectors wired
2025-05-28 route the left connector
2025-05-29 connectors complete!
2025-05-29 start connecting the shift registers
2025-05-29 just starting to route power
2025-05-29 almost there, but when did i delete a display?
2025-05-29 dw the display is fine
2025-05-29 pcb complete!
2025-05-29 add screenshots
2025-05-29 before resistor silkscreen reexport
2025-05-29 re-evaluate BOM
2025-05-29 prepare for submission!
2025-05-29 typo fix (:
2025-06-06 Add BOM to README.md
2025-06-06 Add schematic to README.md
2025-06-11 counting is hard :’)
2025-06-26 cad work
2025-06-27 magazine
2025-06-30 start assembly!
2025-07-01 soldered final resistors (was really annoying)
2025-07-01 markdown is pain (:
2025-07-01 add some tools i used while soldering
2025-07-01 start troubleshooting the thing
2025-07-01 it works!
2025-07-02 debugging progress!
2025-07-02 it works with PIO!
2025-07-02 40x8 working-ish
2025-07-10 one module complete!
2025-07-10 optimize frame computation routine
2025-07-22 journaling
2025-07-29 workkkkk
2025-08-13 it's (back) alive!
2025-08-14 one last hurrah
2025-08-14 add image to readme
